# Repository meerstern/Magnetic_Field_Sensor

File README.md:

# Magnetic_Field_Sensor
Magnetic Field Sensor with DRV425

## 概要 
  * [TI製高感度磁界センサDRV425][1]を使用した高感度磁界センサ基板です  
  * 高感度±0.5mT、帯域最大47kHzで磁界をアナログ出力として得ることができます  
  * シャント抵抗(既定値32ohm)を変更することで±0.1mT~±2.0mTまでの範囲で感度を変更することができます  
  * 地磁気、電流センサ、磁石検出や位置センサの用途に使用することができます  
  * 電源は3.0V～5.5Vで使用できます  
  * センサ出力は電源電圧/2を0mTとして双方向の磁界を検出できます  
  * サイズ14mm x40mm、穴サイズM3x2、間隔22mm  
  
## 注意
  * 電流センサとして使用する場合は2つDRV425を使用して地磁気をキャンセルさせる回路構成にしてください  

  [1]: https://www.tij.co.jp/product/jp/DRV425

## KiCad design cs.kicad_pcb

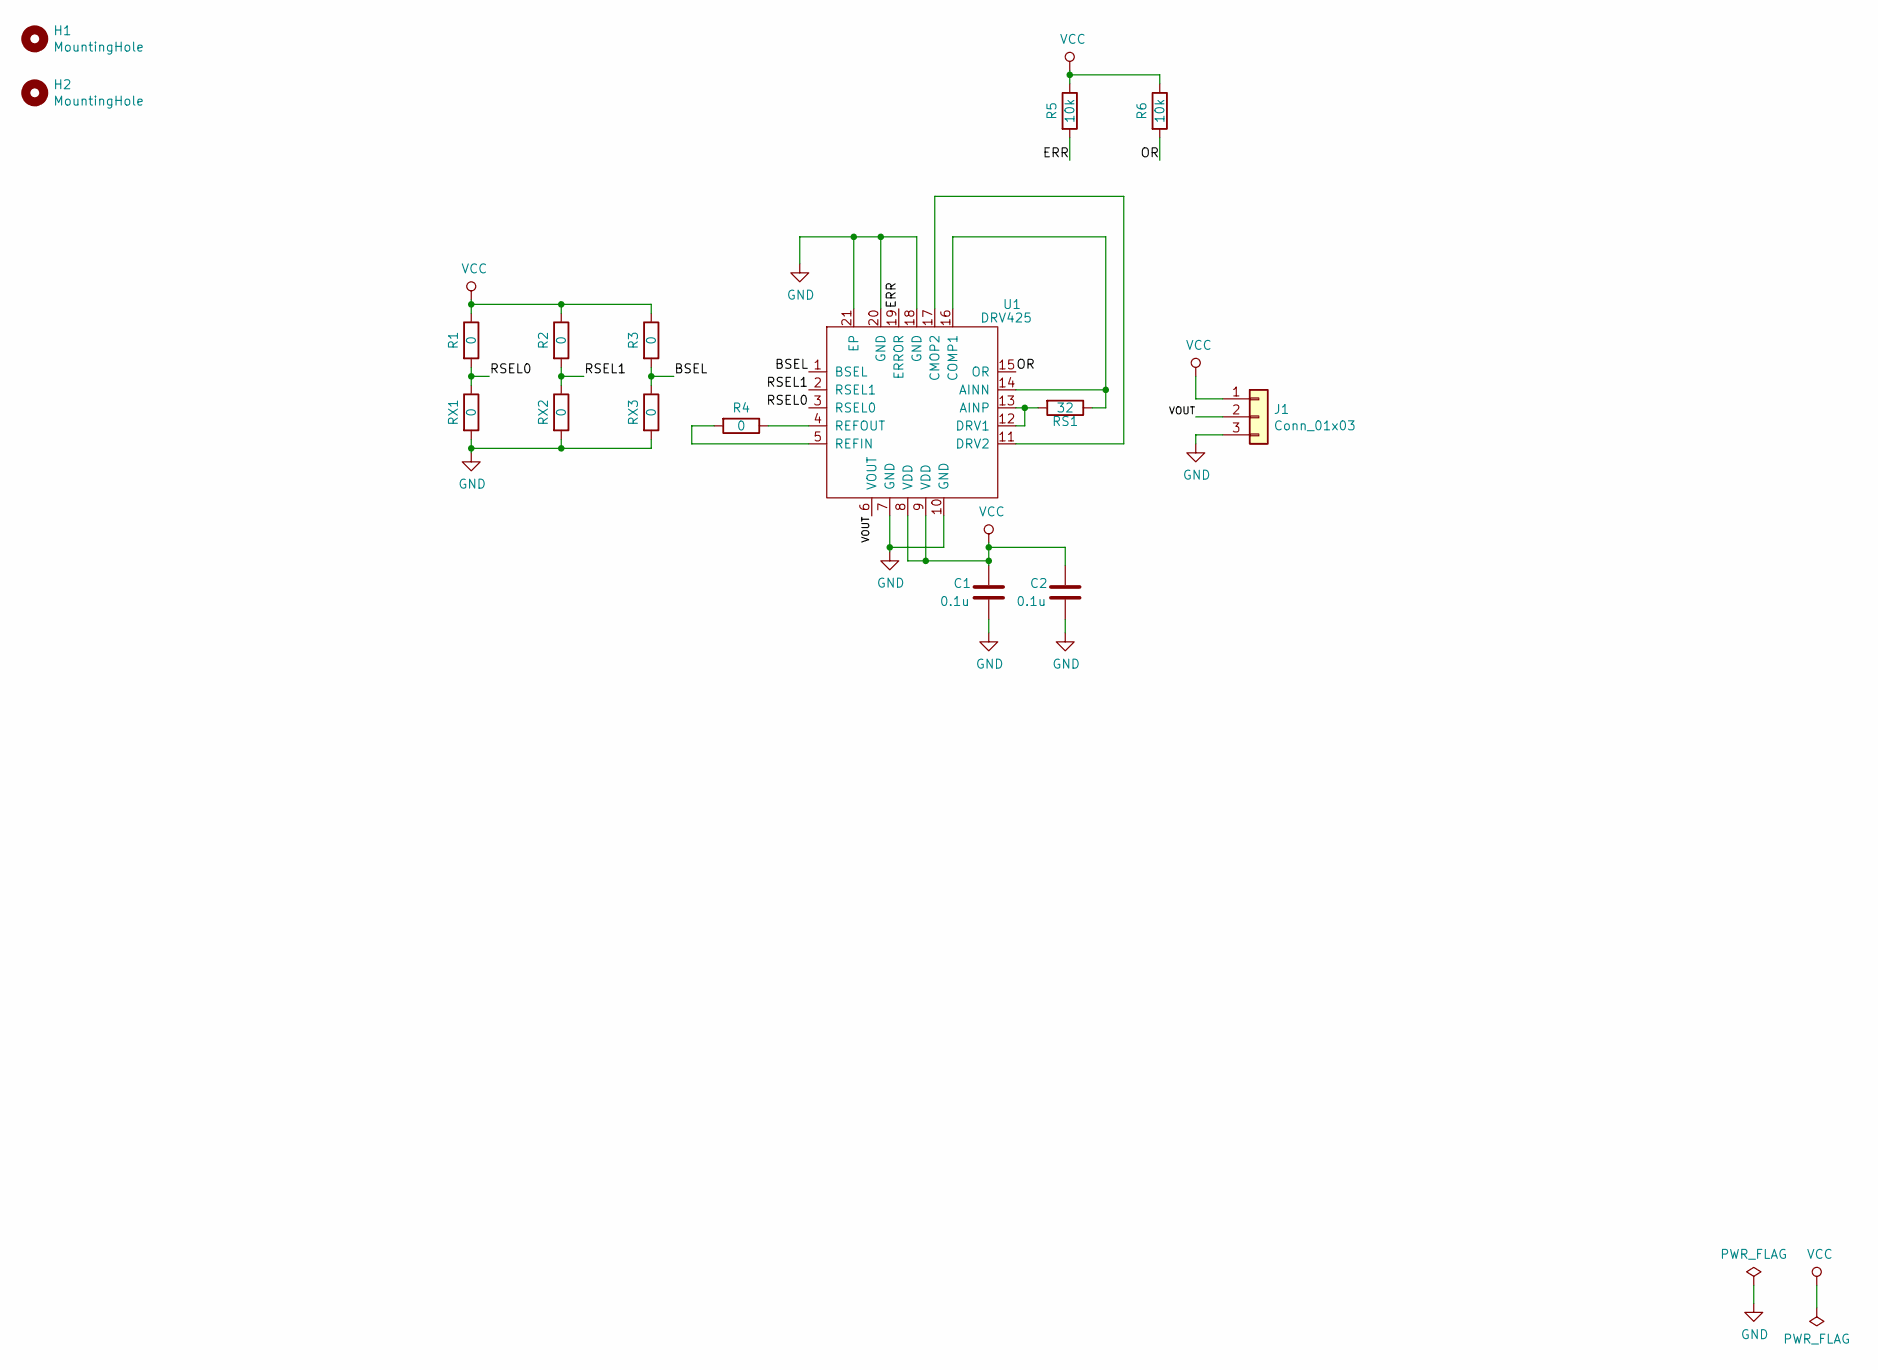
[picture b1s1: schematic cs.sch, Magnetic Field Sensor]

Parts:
C1, C2: 0.1u; C_0603_1608Metric
H1, H2: MountingHole; MountingHole_3.2mm_M3
J1: Conn_01x03; PinHeader_1x03_P2.54mm_Vertical
R1, R2, R3, R4: 0; R_0603_1608Metric
R5, R6: 10k; R_0603_1608Metric
RS1: 32; R_0805_2012Metric
RX1, RX2, RX3: 0; R_0603_1608Metric
U1: DRV425; QFN-20-1EP_4x4mm_P0.5mm_EP2.5x2.5mm_ThermalVias

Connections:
/BSEL: R3.2, RX3.1, U1.1 (BSEL)
/ERR: R5.2, U1.19 (ERROR)
/OR: R6.2, U1.15 (OR)
/RSEL0: R1.2, RX1.1, U1.3 (RSEL0)
/RSEL1: R2.2, RX2.1, U1.2 (RSEL1)
/VOUT: J1.2, U1.6 (VOUT)
GND: C1.2, C2.2, J1.3, RX1.2, RX2.2, RX3.2, U1.7 (GND), U1.10 (GND), U1.18 (GND), U1.20 (GND), U1.21 (EP)
unnamed: R4.1, U1.4 (REFOUT)
unnamed: R4.2, U1.5 (REFIN)
unnamed: RS1.1, U1.14 (AINN), U1.16 (COMP1)
unnamed: RS1.2, U1.12 (DRV1), U1.13 (AINP)
unnamed: U1.11 (DRV2), U1.17 (CMOP2)
VCC: C1.1, C2.1, J1.1, R1.1, R2.1, R3.1, R5.1, R6.1, U1.8 (VDD), U1.9 (VDD)

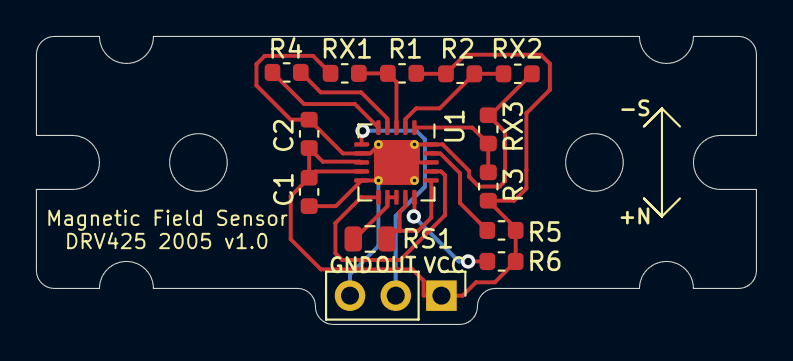
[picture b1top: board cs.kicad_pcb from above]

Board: 2 copper layers, 40.0 x 16.0 mm, 16 parts (0 on the bottom side), 13 nets.

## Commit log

2020-06-07 Add PCB Data
2020-06-17 Add README
2020-07-04 Add img files
